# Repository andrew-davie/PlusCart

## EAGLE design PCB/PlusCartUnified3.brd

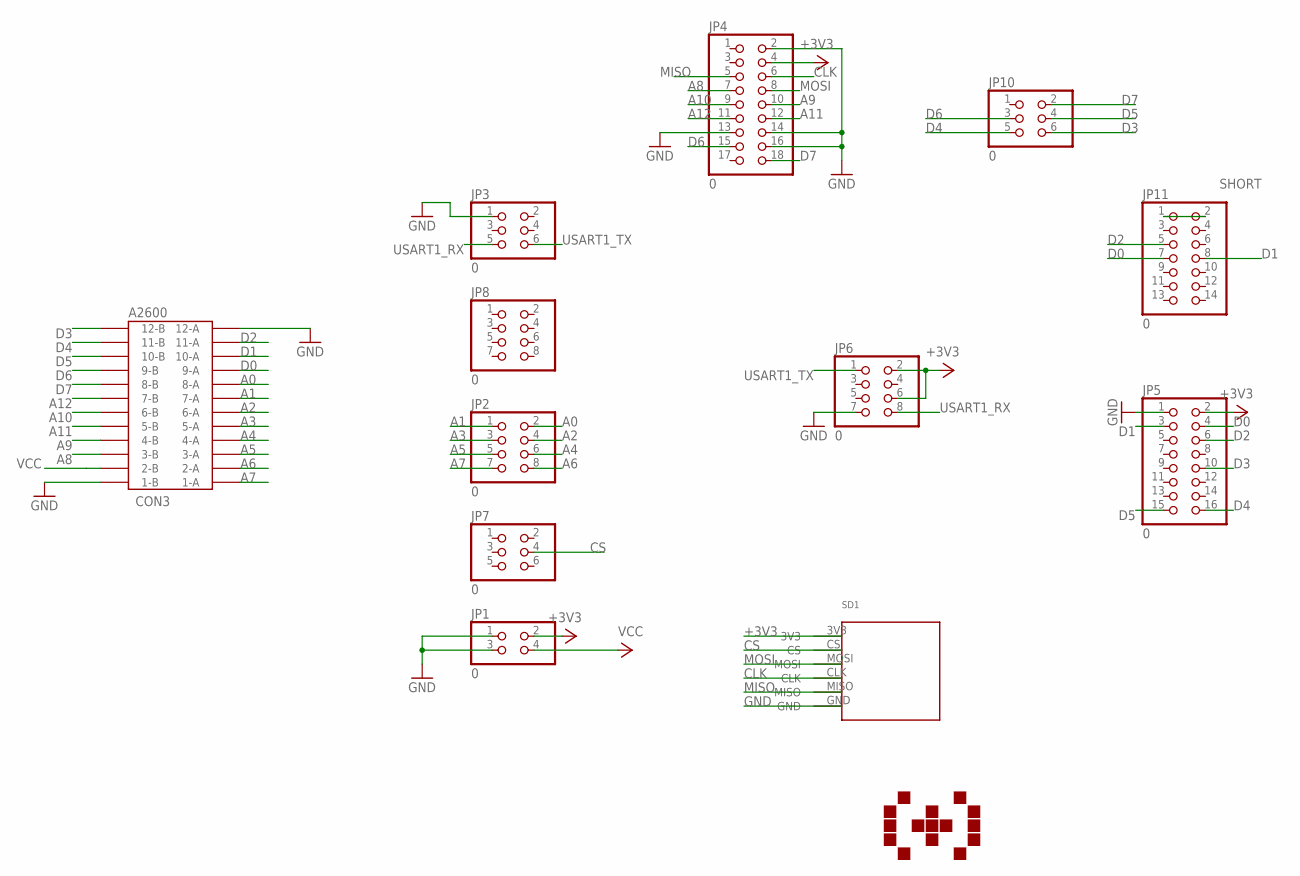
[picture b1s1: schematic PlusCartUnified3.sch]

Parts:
CON3: A2600; 24PINEDGE-254MM
JP1: 0; 2X02
JP2, JP6, JP8: 0; 2X04
JP3, JP7, JP10: 0; 2X03
JP4: 0; 2X09
JP5: 0; 2X08
JP11: 0; 2X07
SD1: MICROSDMICROSD2; MICROSD_FOOTPRINT

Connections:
+3V3: JP1.2, JP4.4, JP5.2, JP6.2, JP6.6, SD1.3V3
A0: CON3.8-A, JP2.2
A1: CON3.7-A, JP2.1
A2: CON3.6-A, JP2.4
A3: CON3.5-A, JP2.3
A4: CON3.4-A, JP2.6
A5: CON3.3-A, JP2.5
A6: CON3.2-A, JP2.8
A7: CON3.1-A, JP2.7
A8: CON3.3-B, JP4.7
A9: CON3.4-B, JP4.10
A10: CON3.6-B, JP4.9
A11: CON3.5-B, JP4.12
A12: CON3.7-B, JP4.11
CLK: JP4.6, SD1.CLK
CS: JP7.4, SD1.CS
D0: CON3.9-A, JP5.4, JP11.7
D1: CON3.10-A, JP5.3, JP11.8
D2: CON3.11-A, JP5.6, JP11.5
D3: CON3.12-B, JP5.10, JP10.6
D4: CON3.11-B, JP5.16, JP10.5
D5: CON3.10-B, JP5.15, JP10.4
D6: CON3.9-B, JP4.15, JP10.3
D7: CON3.8-B, JP4.18, JP10.2
GND: CON3.1-B, CON3.12-A, JP1.1, JP1.3, JP3.1, JP4.2, JP4.13, JP4.14, JP4.16, JP5.1, JP6.7, SD1.GND
MISO: JP4.5, SD1.MISO
MOSI: JP4.8, SD1.MOSI
SHORT: JP11.1, JP11.2
USART1_RX: JP3.5, JP6.8
USART1_TX: JP3.6, JP6.1
VCC: CON3.2-B, JP1.4

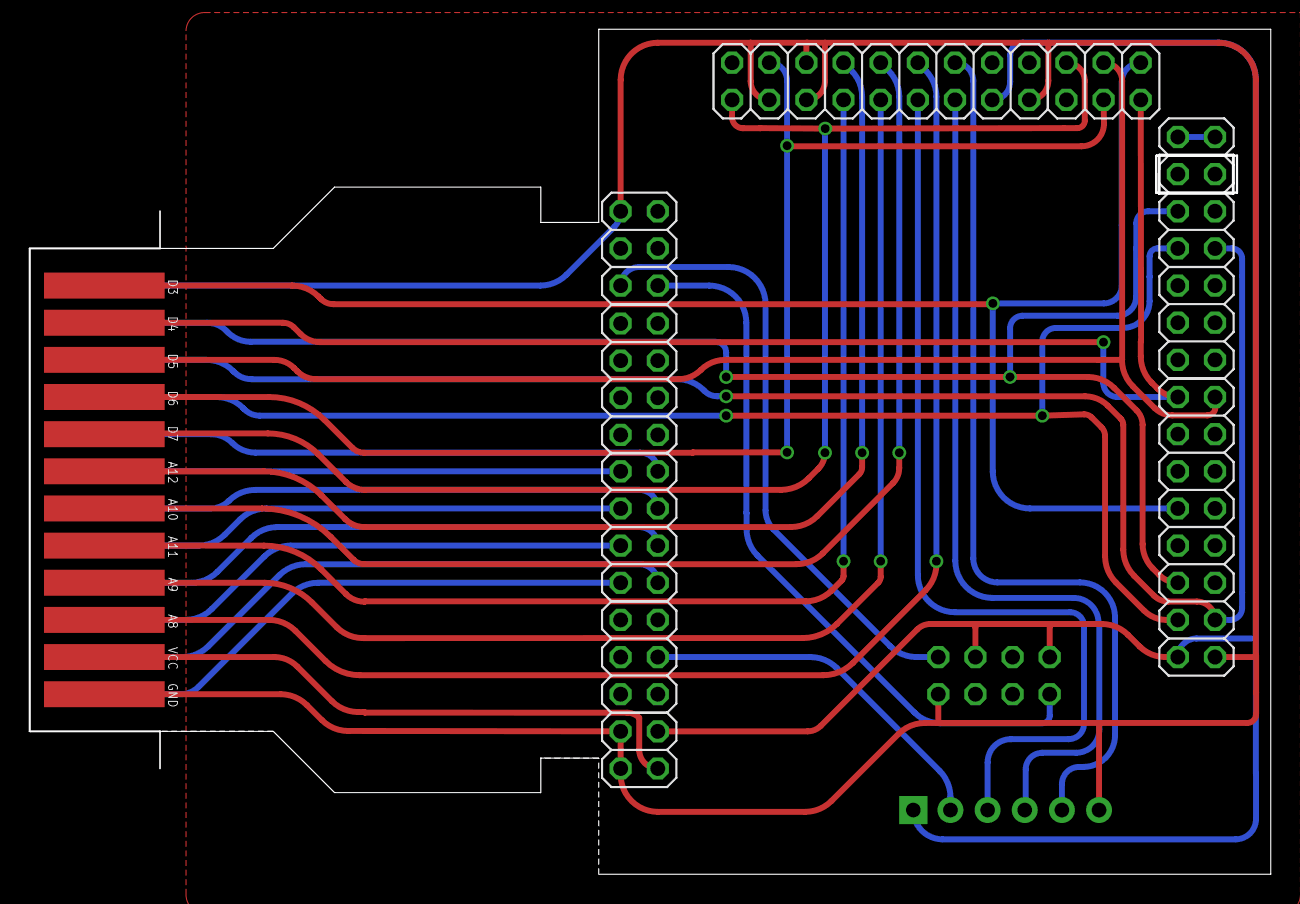
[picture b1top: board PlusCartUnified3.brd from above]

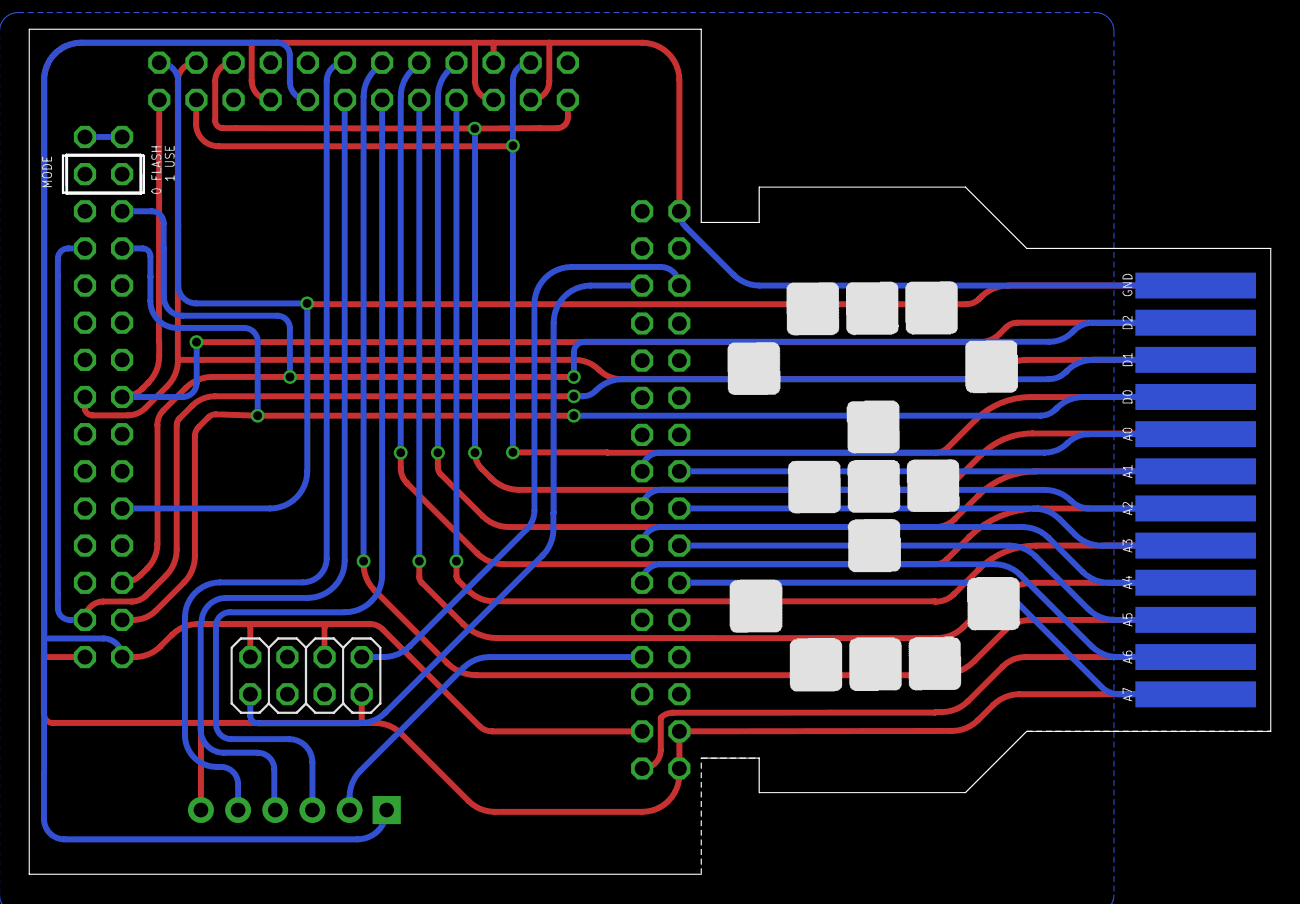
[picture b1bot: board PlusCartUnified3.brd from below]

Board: 2 copper layers, 84.7 x 57.6 mm, 12 parts (3 on the bottom side), 31 nets.

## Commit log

2021-07-21 PlusCart
2021-07-21 STL files added
2021-08-27 Fixes to rigidity and sizing
    * the shell is 0.5mm wider to accomodate variance in cartridge slot fit.
    * the logo is once again printed "in situ" rather than as a post-print glue-in. This requires a filament swap during print, but in the long run it's not much more pain than welding/gluing in the logo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
    * The tensioner "ramps" at the bottom of the cart are removed - again, allowing for cartridge slot variance
    * the "rail", or "lip" as I call it, is now exactly 1.6 mm wide, allowing a 0.4 mm slice to fit in 4 rows. This makes them super strong. The lip both masks the join but also acts as a first-stage she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
2021-08-27 added SD variant of shell FRONT
2022-03-02 cleanup
    fixed for some problematic JRs, with looser spacing around shell exterior
    Duo variant (front only is different) added in STLs
2022-04-14 redesigned following AL issues with sizing
2022-09-14 quick-n-dirty push of latest. will fix later.
